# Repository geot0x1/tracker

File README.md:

# Revision 1 [R1]

### Known issues

The 3.3V power supply remains disabled by the battery charger, which pulls the EN pin low with the PG pin. It must be inverted using a BJT.  

Battery connector pins is wrong.  

Crystal has wrong footprint.  

Memory footprint is wrong, too big for the part.  

RX and TX lines on GSM connection are swapped.  

Change the programming port to 1.5mm pitch.

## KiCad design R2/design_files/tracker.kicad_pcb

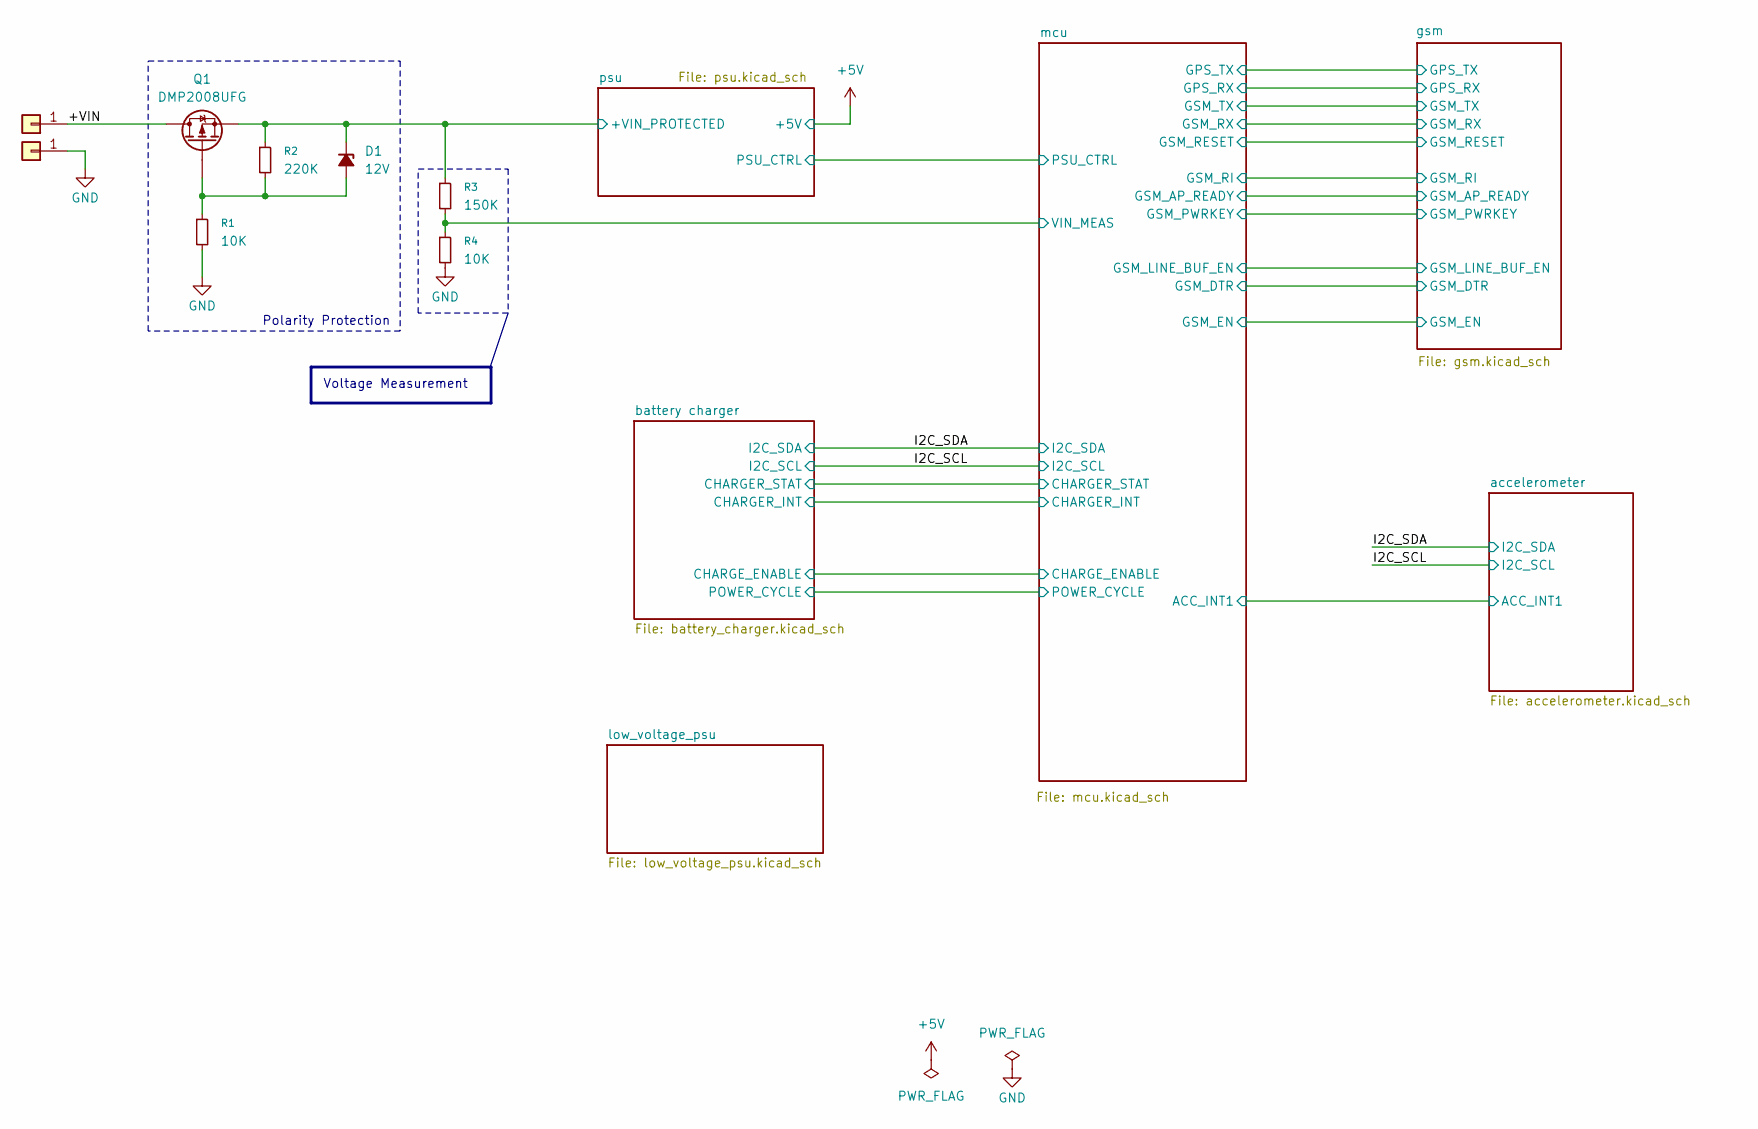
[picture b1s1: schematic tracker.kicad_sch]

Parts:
D1: 12V; D_SOD-323; PartNo PDZ12B,115
J1, J2: Conn_01x01; pad_smd_1.5x3
Q1: DMP2008UFG; Diodes_PowerDI3333-8
R1, R4: 10K; R_0603_1608Metric
R2: 220K; R_0603_1608Metric
R3: 150K; R_0603_1608Metric

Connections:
/+VIN: J1.1 (Pin_1_1), Q1.5 (D)
/mcu/VIN_MEAS: R3.2, R4.1; also elsewhere on the board
/psu/+VIN_PROTECTED: D1.1 (K), Q1.1 (S), Q1.2 (S), Q1.3 (S), R2.1, R3.1; also elsewhere on the board
GND: J2.1 (Pin_1_1), R1.2, R4.2; also elsewhere on the board
unnamed: D1.2 (A), Q1.4 (G), R1.1, R2.2

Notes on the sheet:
Polarity Protection
Voltage Measurement

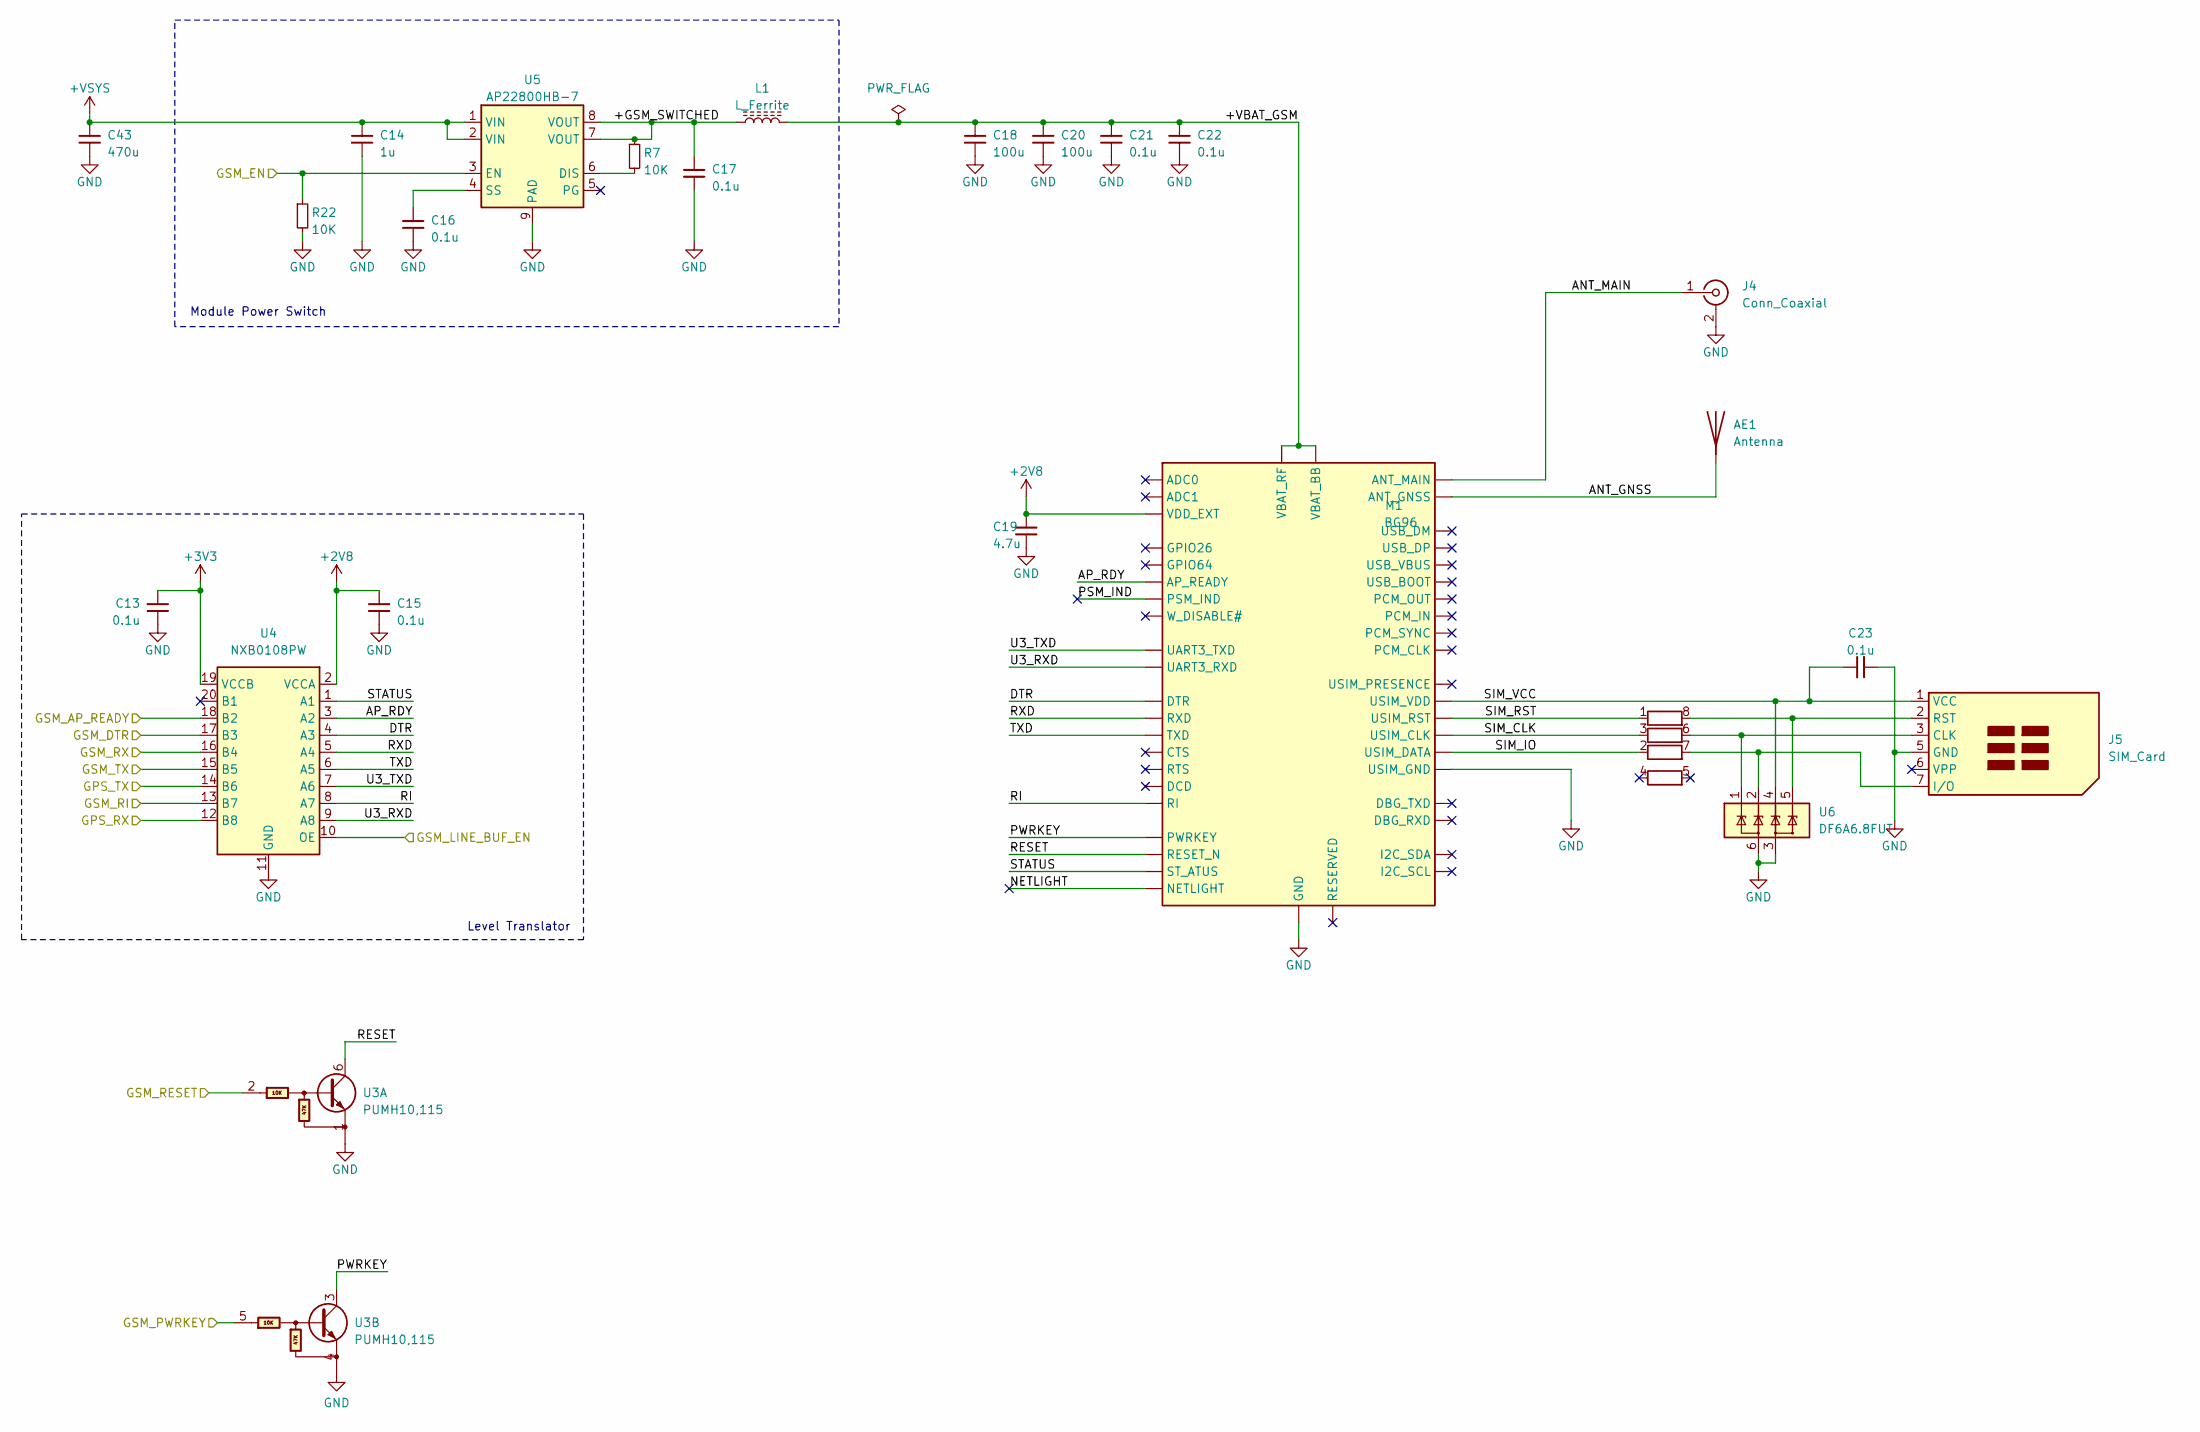
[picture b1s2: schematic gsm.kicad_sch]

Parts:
AE1: Antenna; APAE1575R1820ABDC1
C13, C15, C16, C17, C21, C22, C23: 0.1u; C_0603_1608Metric
C14: 1u; C_0603_1608Metric
C18, C20: 100u; CP_EIA-6032-20_AVX-F
C19: 4.7u; C_0603_1608Metric
C43: 470u; CP_EIA-7343-31_Kemet-D
J4: Conn_Coaxial; U.FL_Molex_MCRF_73412-0110_Vertical
J5: SIM_Card; microSIM_JAE_SF53S006VCBR2000
L1: L_Ferrite; L_0805_2012Metric
M1: BG96; LGA_BG96
R7, R22: 10K; R_0402_1005Metric
RN1: 22R; R_Array_Concave_4x0603
U3: PUMH10,115; SOT-363_SC-70-6
U4: NXB0108PW; TSSOP-20_4.4x6.5mm_P0.65mm
U5: AP22800HB-7; UDFN2116-8_Diodes
U6: DF6A6.8FUT; SOT-363_SC-70-6

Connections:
+2V8: C15.1, C19.1, M1.29 (VDD_EXT), U4.2 (VCCA)
+3V3: C13.1, U4.19 (VCCB); also elsewhere on the board
+VSYS: C14.1, C43.1, U5.1 (VIN), U5.2 (VIN); also elsewhere on the board
/gsm/+GSM_SWITCHED: C17.1, L1.1, R7.1, U5.7 (VOUT), U5.8 (VOUT)
/gsm/+VBAT_GSM: C18.1, C20.1, C21.1, C22.1, L1.2, M1.32 (VBAT_BB), M1.33 (VBAT_BB), M1.52 (VBAT_RF), M1.53 (VBAT_RF), M1.[32,33] (VBAT_BB), M1.[52,53] (VBAT_RF)
/gsm/ANT_GNSS: AE1.1 (A_1), M1.49 (ANT_GNSS)
/gsm/ANT_MAIN: J4.1 (In), M1.60 (ANT_MAIN)
/gsm/AP_RDY: M1.19 (AP_READY), U4.3 (A2)
/gsm/DTR: M1.30 (DTR), U4.4 (A3)
/gsm/GPS_RX: U4.12 (B8); also elsewhere on the board
/gsm/GPS_TX: U4.14 (B6); also elsewhere on the board
/gsm/GSM_AP_READY: U4.18 (B2); also elsewhere on the board
/gsm/GSM_DTR: U4.17 (B3); also elsewhere on the board
/gsm/GSM_EN: R22.1, U5.3 (EN); also elsewhere on the board
/gsm/GSM_LINE_BUF_EN: U4.10 (OE); also elsewhere on the board
/gsm/GSM_PWRKEY: U3.5; also elsewhere on the board
/gsm/GSM_RESET: U3.2; also elsewhere on the board
/gsm/GSM_RI: U4.13 (B7); also elsewhere on the board
/gsm/GSM_RX: U4.16 (B4); also elsewhere on the board
/gsm/GSM_TX: U4.15 (B5); also elsewhere on the board
/gsm/NETLIGHT: M1.21 (NETLIGHT)
/gsm/PSM_IND: M1.1 (PSM_IND)
/gsm/PWRKEY: M1.15 (PWRKEY), U3.3
/gsm/RESET: M1.17 (RESET_N), U3.6
/gsm/RI: M1.39 (RI), U4.8 (A7)
/gsm/RXD: M1.34 (RXD), U4.5 (A4)
/gsm/SIM_CLK: M1.46 (USIM_CLK), RN1.3 (R3.1)
/gsm/SIM_IO: M1.45 (USIM_DATA), RN1.2 (R2.1)
/gsm/SIM_RST: M1.44 (USIM_RST), RN1.1 (R1.1)
/gsm/SIM_VCC: C23.1, J5.1 (VCC), M1.43 (USIM_VDD), U6.4 (IO3)
/gsm/STATUS: M1.20 (ST_ATUS), U4.1 (A1)
/gsm/TXD: M1.35 (TXD), U4.6 (A5)
/gsm/U3_RXD: M1.28 (UART3_RXD), U4.9 (A8)
/gsm/U3_TXD: M1.27 (UART3_TXD), U4.7 (A6)
GND: C13.2, C14.2, C15.2, C16.2, C17.2, C18.2, C19.2, C20.2, C21.2, C22.2, C23.2, C43.2, J4.2 (Ext), J5.5 (GND), M1.3 (GND), M1.31 (GND), M1.47 (USIM_GND), M1.48 (GND), M1.50 (GND), M1.54 (GND), M1.55 (GND), M1.58 (GND), M1.59 (GND), M1.61 (GND), M1.62 (GND), M1.67 (GND), M1.68 (GND), M1.69 (GND), M1.70 (GND), M1.71 (GND), M1.72 (GND), M1.73 (GND), M1.74 (GND), M1.79 (GND), M1.80 (GND), M1.81 (GND), M1.82 (GND), M1.89 (GND), M1.90 (GND), M1.91 (GND), M1.100 (GND), M1.101 (GND), M1.102 (GND), M1.[3,31,48,50,54,55,5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 (GND), R22.2, U3.1, U3.4, U4.11 (GND), U5.9 (PAD), U6.3 (GND), U6.6 (GND); also elsewhere on the board
unnamed: J5.3 (CLK), RN1.6 (R3.2), U6.1 (IO1)
unnamed: J5.7 (I/O), RN1.7 (R2.2), U6.2 (IO2)
unnamed: J5.2 (RST), RN1.8 (R1.2), U6.5 (IO4)
unnamed: R7.2, U5.6 (DIS)
unnamed: C16.1, U5.4 (SS)

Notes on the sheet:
Module Power Switch
Level Translator

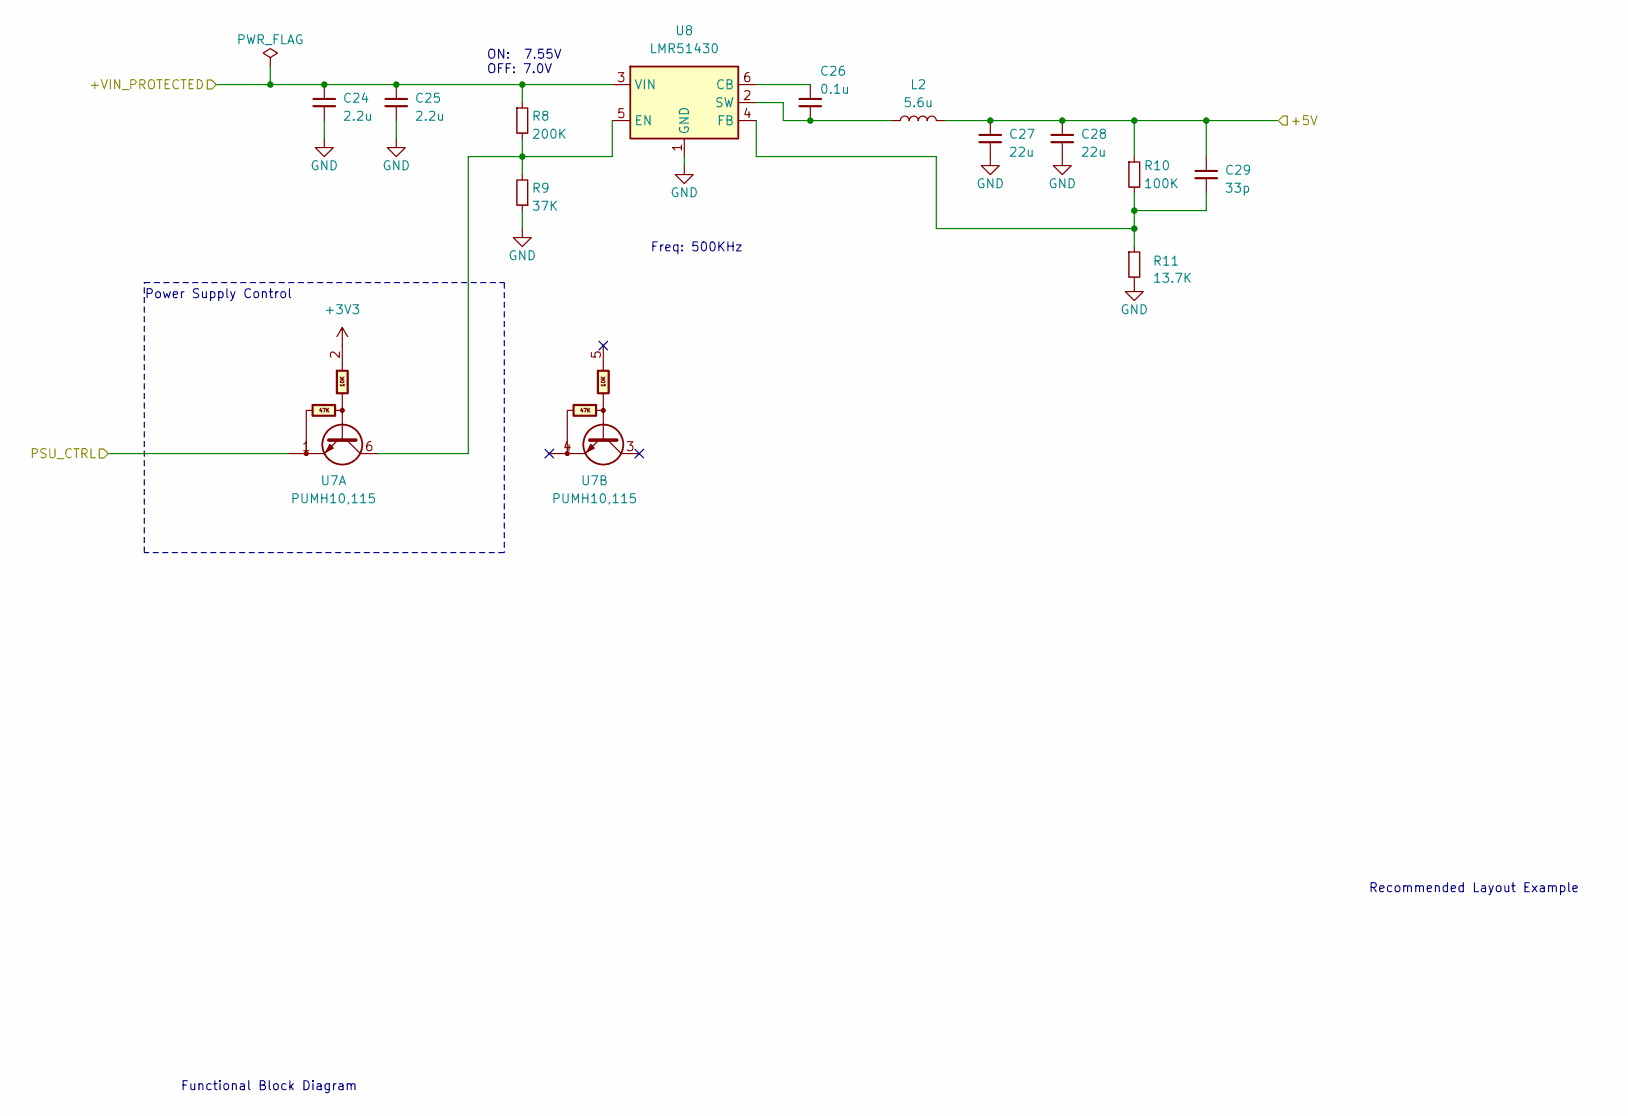
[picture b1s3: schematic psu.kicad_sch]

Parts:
C24, C25: 2.2u; C_1210_3225Metric
C26: 0.1u; C_0603_1608Metric
C27, C28: 22u; C_1210_3225Metric
C29: 33p; C_0402_1005Metric
L2: 5.6u; L_Bourns_SRN8040TA; Part No SRN8040TA-5R6M
R8: 200K; R_0402_1005Metric
R9: 37K; R_0402_1005Metric
R10: 100K; R_0402_1005Metric
R11: 13.7K; R_0402_1005Metric
U7: PUMH10,115; SOT-363_SC-70-6
U8: LMR51430; SOT-23-6

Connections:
+3V3: U7.2; also elsewhere on the board
+5V: C27.1, C28.1, C29.1, L2.2, R10.1; also elsewhere on the board
/mcu/PSU_CTRL: U7.1; also elsewhere on the board
/psu/+VIN_PROTECTED: C24.1, C25.1, R8.1, U8.3 (VIN); also elsewhere on the board
GND: C24.2, C25.2, C27.2, C28.2, R9.1, R11.2, U8.1 (GND); also elsewhere on the board
unnamed: C26.1, U8.6 (CB)
unnamed: R8.2, R9.2, U7.6, U8.5 (EN)
unnamed: C29.2, R10.2, R11.1, U8.4 (FB)
unnamed: C26.2, L2.1, U8.2 (SW)

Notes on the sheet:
Freq: 500KHz
Functional Block Diagram
ON: 7.55V OFF: 7.0V
Power Supply Control
Recommended Layout Example

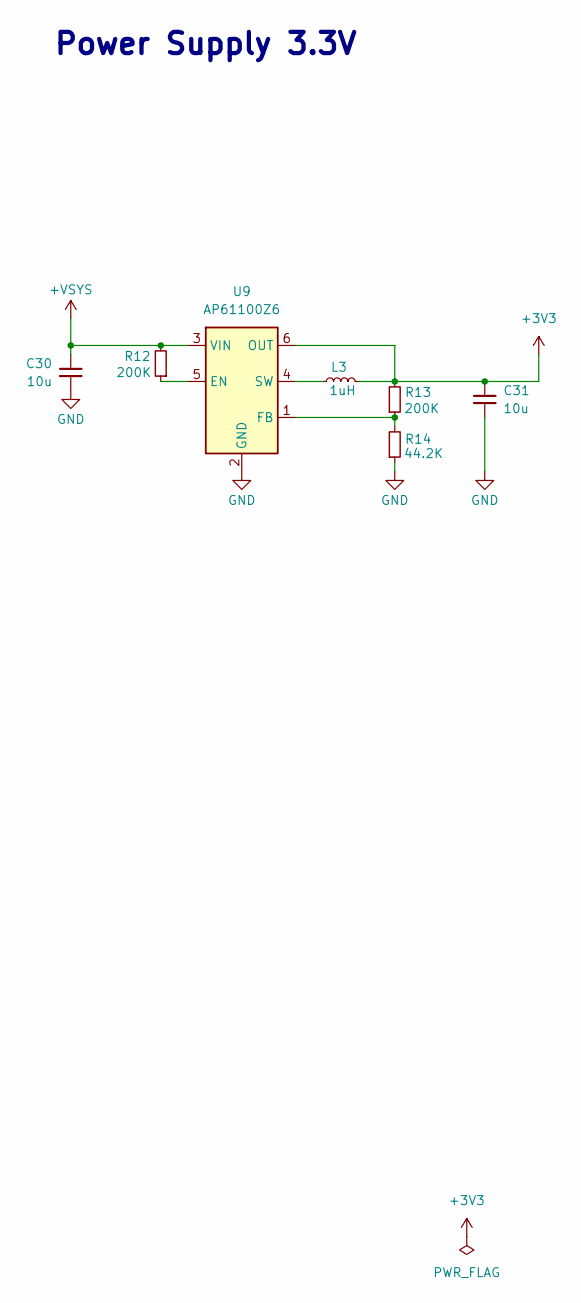
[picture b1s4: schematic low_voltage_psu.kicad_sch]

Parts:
C30, C31: 10u; C_0805_2012Metric
L3: 1uH; L_0806_2016Metric_TAIYO_YUDEN_SMD; PartNo MAKK2016T1R0M
R12, R13: 200K; R_0402_1005Metric
R14: 44.2K; R_0402_1005Metric
U9: AP61100Z6; SOT-563

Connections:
+3V3: C31.1, L3.2, R13.2, U9.6 (OUT); also elsewhere on the board
+VSYS: C30.1, R12.2, U9.3 (VIN); also elsewhere on the board
GND: C30.2, C31.2, R14.1, U9.2 (GND); also elsewhere on the board
unnamed: R12.1, U9.5 (EN)
unnamed: R13.1, R14.2, U9.1 (FB)
unnamed: L3.1, U9.4 (SW)

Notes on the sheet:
Power Supply 3.3V

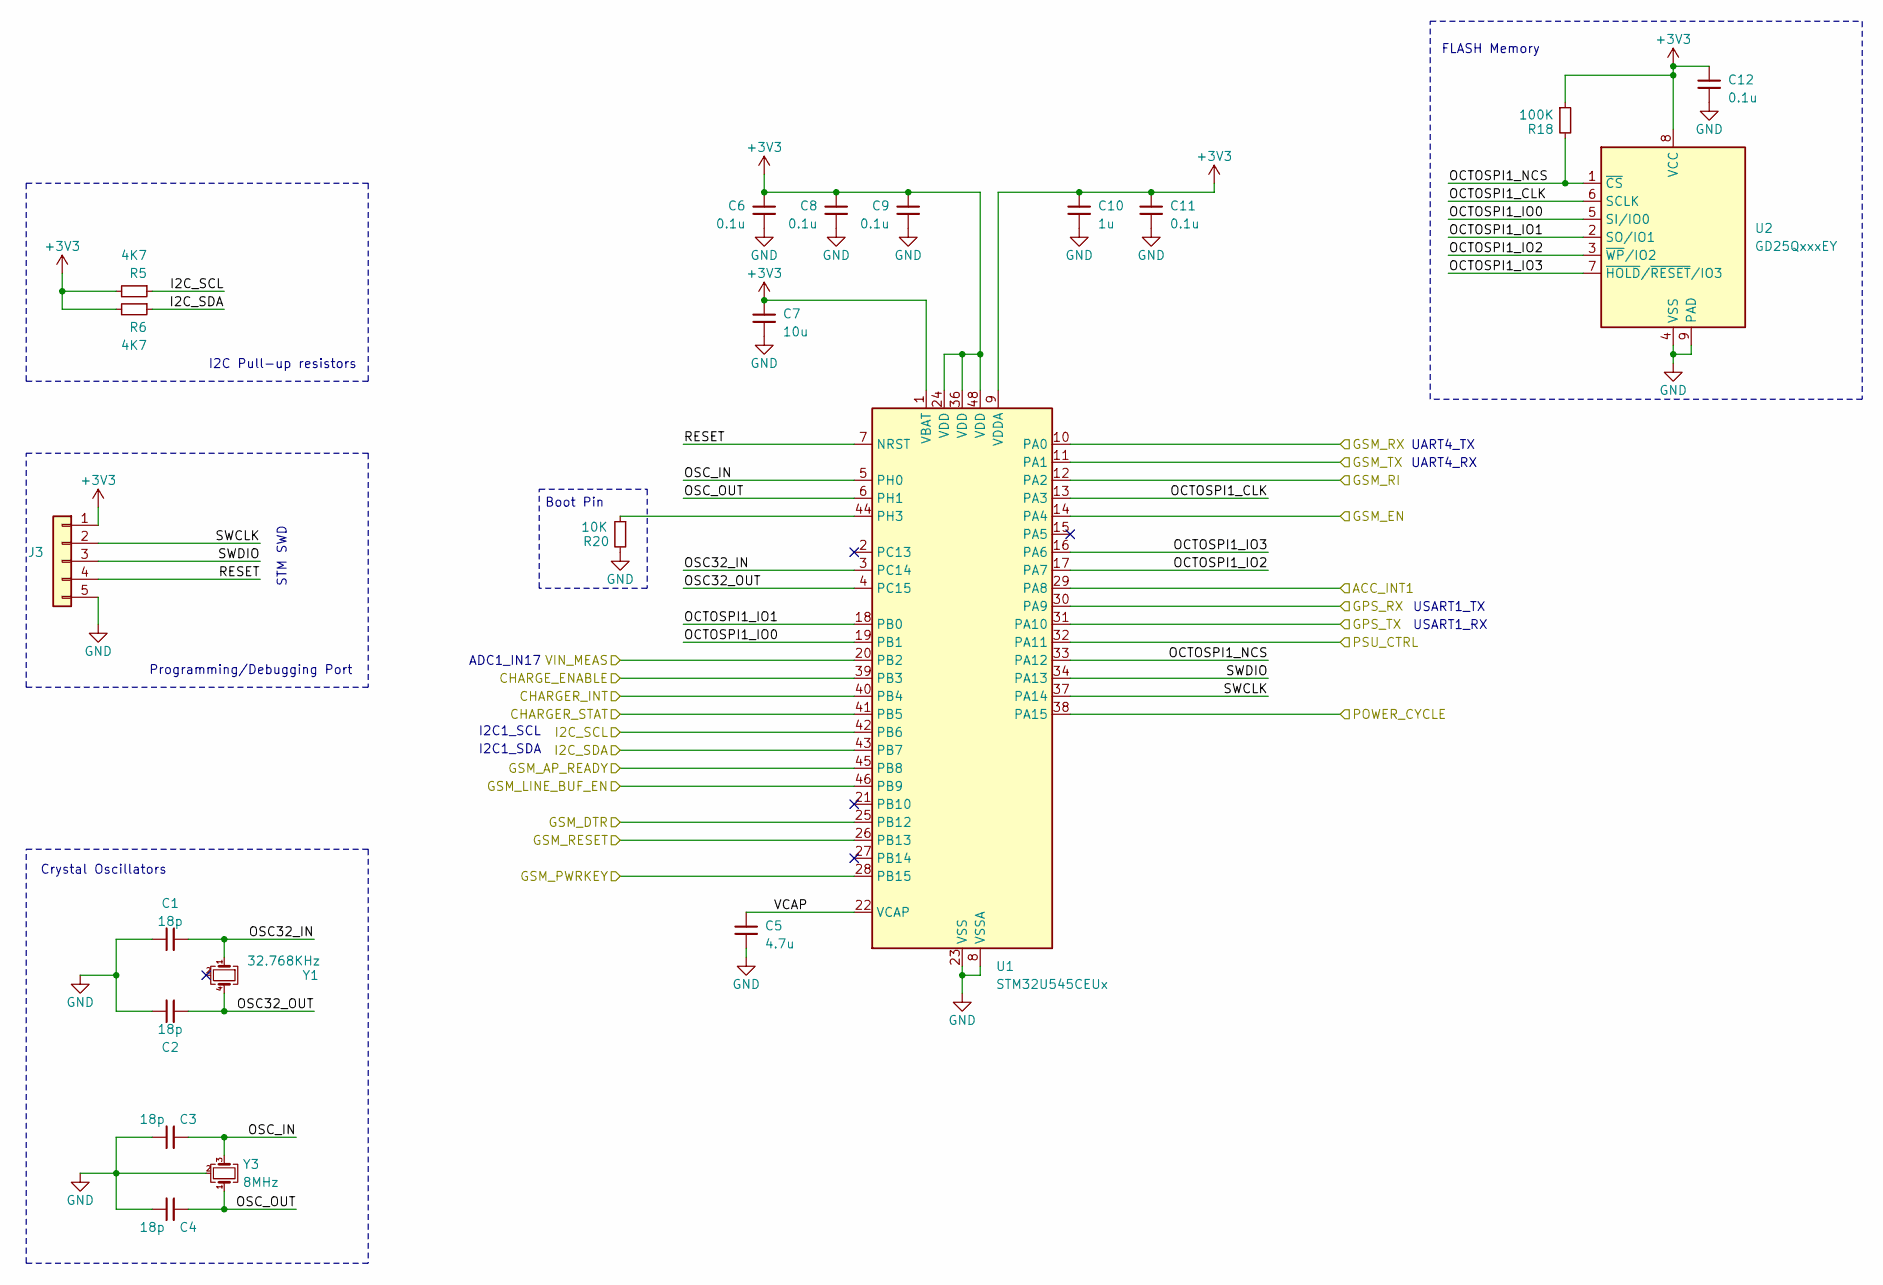
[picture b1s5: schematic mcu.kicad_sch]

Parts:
C1, C2, C3, C4: 18p; C_0402_1005Metric
C5: 4.7u; C_0603_1608Metric
C6, C8, C9, C11, C12: 0.1u; C_0603_1608Metric
C7: 10u; C_0805_2012Metric
C10: 1u; C_0603_1608Metric
J3: Conn_01x05; JST_PH_B5B-PH-SM4-TB_1x05-1MP_P2.00mm_Vertical
R5, R6: 4K7; R_0402_1005Metric
R18: 100K; R_0402_1005Metric
R20: 10K; R_0402_1005Metric
U1: STM32U545CEUx; QFN-48-1EP_7x7mm_P0.5mm_EP5.6x5.6mm
U2: GD25QxxxEY; WSON-8-1EP_8x6mm_P1.27mm_EP3.4x4.3mm
Y1: 32.768KHz; Crystal_SMD_SeikoEpson_MC146-4Pin_6.7x1.5mm
Y3: 8MHz; Crystal_SMD_SeikoEpson_FA238-4Pin_3.2x2.5mm; JLCPCB C49158086

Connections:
+3V3: C6.1, C7.1, C8.1, C9.1, C10.1, C11.1, C12.1, J3.1, R5.2, R6.2, R18.1, U1.1 (VBAT), U1.9 (VDDA), U1.24 (VDD), U1.36 (VDD), U1.48 (VDD), U2.8 (VCC); also elsewhere on the board
/I2C_SCL: R5.1, U1.42 (PB6); also elsewhere on the board
/I2C_SDA: R6.1, U1.43 (PB7); also elsewhere on the board
/accelerometer/ACC_INT1: U1.29 (PA8); also elsewhere on the board
/battery charger/CHARGER_INT: U1.40 (PB4); also elsewhere on the board
/battery charger/CHARGER_STAT: U1.41 (PB5); also elsewhere on the board
/battery charger/CHARGE_ENABLE: U1.39 (PB3); also elsewhere on the board
/battery charger/POWER_CYCLE: U1.38 (PA15); also elsewhere on the board
/gsm/GPS_RX: U1.30 (PA9); also elsewhere on the board
/gsm/GPS_TX: U1.31 (PA10); also elsewhere on the board
/gsm/GSM_AP_READY: U1.45 (PB8); also elsewhere on the board
/gsm/GSM_DTR: U1.25 (PB12); also elsewhere on the board
/gsm/GSM_EN: U1.14 (PA4); also elsewhere on the board
/gsm/GSM_LINE_BUF_EN: U1.46 (PB9); also elsewhere on the board
/gsm/GSM_PWRKEY: U1.28 (PB15); also elsewhere on the board
/gsm/GSM_RESET: U1.26 (PB13); also elsewhere on the board
/gsm/GSM_RI: U1.12 (PA2); also elsewhere on the board
/gsm/GSM_RX: U1.10 (PA0); also elsewhere on the board
/gsm/GSM_TX: U1.11 (PA1); also elsewhere on the board
/mcu/OCTOSPI1_CLK: U1.13 (PA3), U2.6 (SCLK)
/mcu/OCTOSPI1_IO0: U1.19 (PB1), U2.5 (SI/IO0)
/mcu/OCTOSPI1_IO1: U1.18 (PB0), U2.2 (SO/IO1)
/mcu/OCTOSPI1_IO2: U1.17 (PA7), U2.3 (~WP/IO2)
/mcu/OCTOSPI1_IO3: U1.16 (PA6), U2.7 (~HOLD/~RESET/IO3)
/mcu/OCTOSPI1_NCS: R18.2, U1.33 (PA12), U2.1 (~CS)
/mcu/OSC32_IN: C1.2, U1.3 (PC14), Y1.1
/mcu/OSC32_OUT: C2.1, U1.4 (PC15), Y1.4
/mcu/OSC_IN: C3.2, U1.5 (PH0), Y3.3
/mcu/OSC_OUT: C4.2, U1.6 (PH1), Y3.1
/mcu/PSU_CTRL: U1.32 (PA11); also elsewhere on the board
/mcu/RESET: J3.4, U1.7 (NRST)
/mcu/SWCLK: J3.2, U1.37 (PA14)
/mcu/SWDIO: J3.3, U1.34 (PA13)
/mcu/VCAP: C5.1, U1.22 (VCAP)
/mcu/VIN_MEAS: U1.20 (PB2); also elsewhere on the board
GND: C1.1, C2.2, C3.1, C4.1, C5.2, C6.2, C7.2, C8.2, C9.2, C10.2, C11.2, C12.2, J3.5, R20.2, U1.8 (VSSA), U1.23 (VSS), U1.35 (VSS), U1.47 (VSS), U1.49 (VSS), U2.4 (VSS), U2.9 (PAD), Y3.2 (G), Y3.4 (G); also elsewhere on the board
unnamed: R20.1, U1.44 (PH3)

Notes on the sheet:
USART1_RX
UART4_TX
STM SWD
Boot Pin
I2C1_SCL
I2C1_SDA
Crystal Oscillators
UART4_RX
USART1_TX
Programming/Debugging Port
FLASH Memory
ADC1_IN17
I2C Pull-up resistors

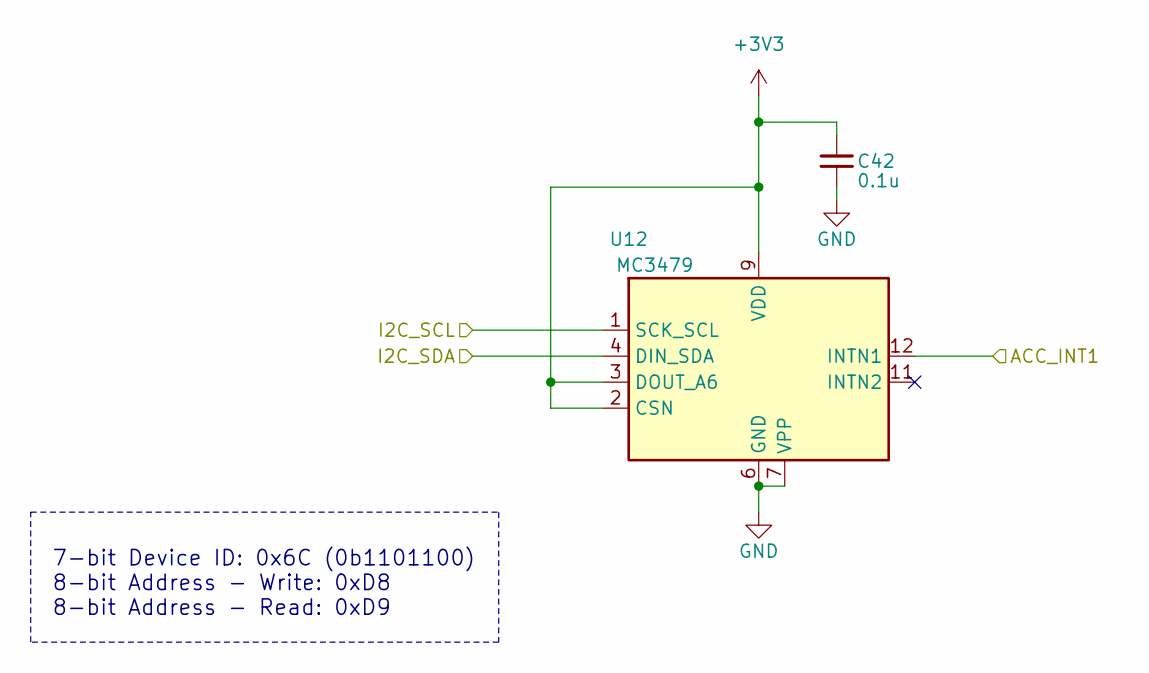
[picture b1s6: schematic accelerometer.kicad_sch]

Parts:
C42: 0.1u; C_0603_1608Metric
U12: MC3479; LGA-12_2x2mm_P0.5mm

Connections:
+3V3: C42.1, U12.2 (CSN), U12.3 (DOUT_A6), U12.9 (VDD); also elsewhere on the board
/I2C_SCL: U12.1 (SCK_SCL); also elsewhere on the board
/I2C_SDA: U12.4 (DIN_SDA); also elsewhere on the board
/accelerometer/ACC_INT1: U12.12 (INTN1); also elsewhere on the board
GND: C42.2, U12.6 (GND), U12.7 (VPP); also elsewhere on the board

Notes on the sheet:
7-bit Device ID: 0x6C (0b1101100) 8-bit Address - Write: 0xD8 8-bit Address - Read: 0xD9

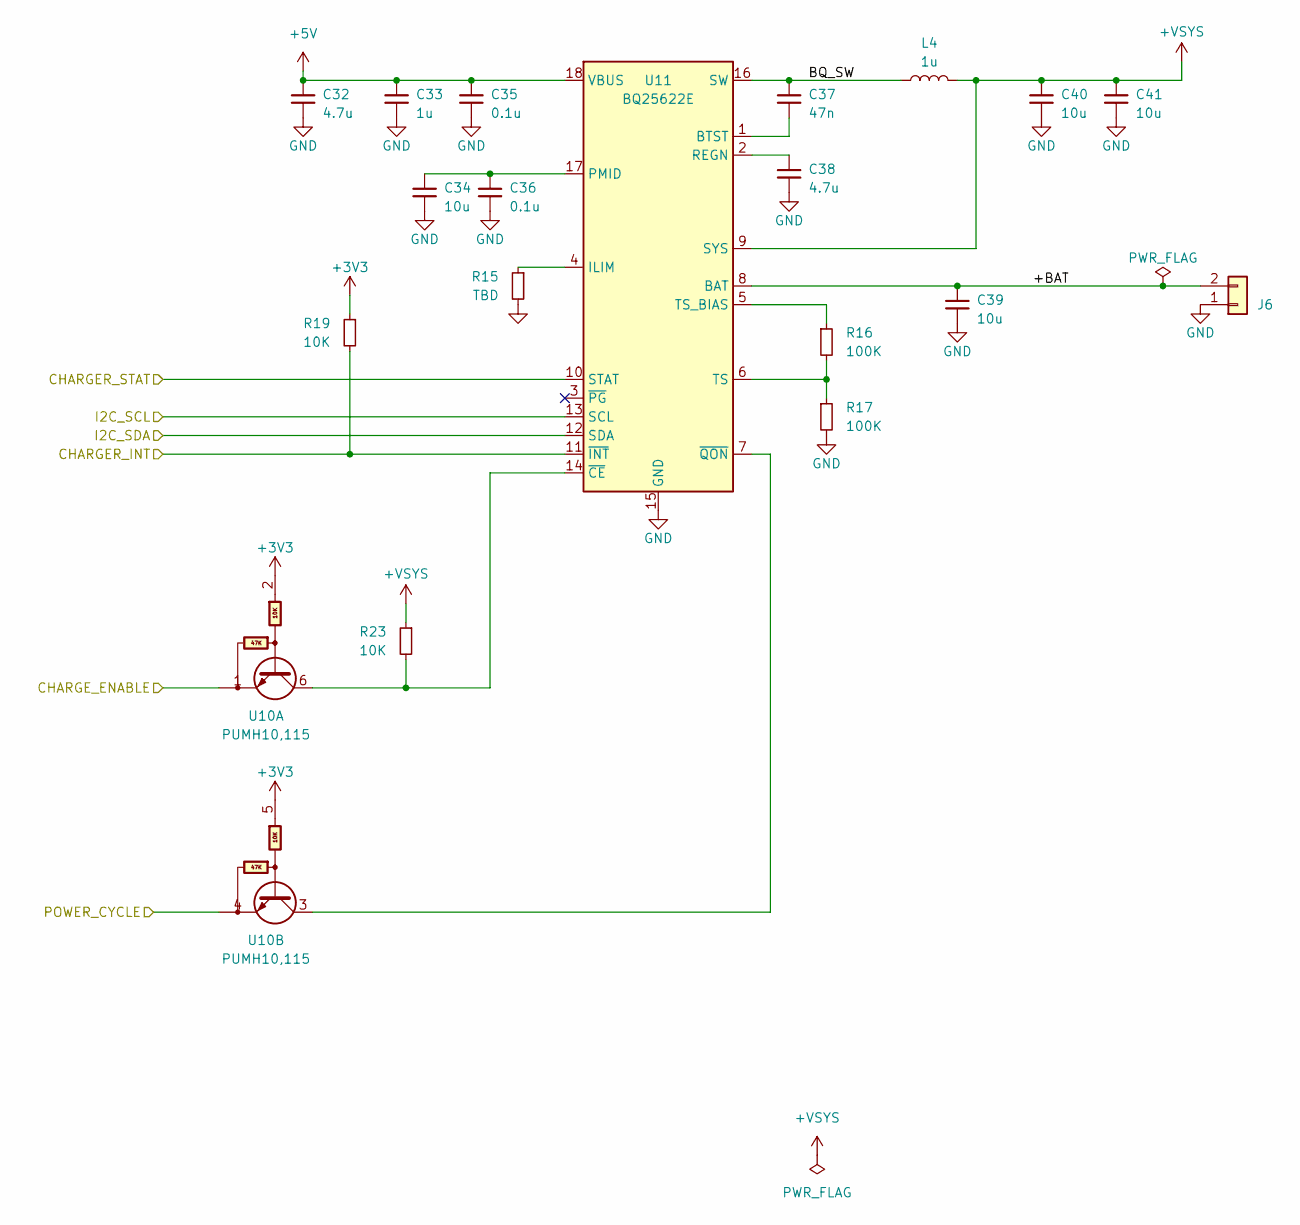
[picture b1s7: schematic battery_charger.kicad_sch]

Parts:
C32: 4.7u; C_0805_2012Metric
C33: 1u; C_0603_1608Metric
C34, C39, C40, C41: 10u; C_0805_2012Metric
C35, C36: 0.1u; C_0603_1608Metric
C37: 47n; C_0402_1005Metric
C38: 4.7u; C_0603_1608Metric
J6: Conn_01x02; JST_XH_B2B-XH-A_1x02_P2.50mm_Vertical
L4: 1u; Inductor_TYA252012
R15: TBD; R_0402_1005Metric
R16, R17: 100K; R_0402_1005Metric
R19, R23: 10K; R_0402_1005Metric
U10: PUMH10,115; SOT-363_SC-70-6
U11: BQ25622E

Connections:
+3V3: R19.1, U10.2, U10.5; also elsewhere on the board
+5V: C32.1, C33.1, C35.1, U11.18 (VBUS); also elsewhere on the board
+VSYS: C40.1, C41.1, L4.2, R23.1, U11.9 (SYS); also elsewhere on the board
/I2C_SCL: U11.13 (SCL); also elsewhere on the board
/I2C_SDA: U11.12 (SDA); also elsewhere on the board
/battery charger/+BAT: C39.1, J6.2, U11.8 (BAT)
/battery charger/BQ_SW: C37.1, L4.1, U11.16 (SW)
/battery charger/CHARGER_INT: R19.2, U11.11 (~INT); also elsewhere on the board
/battery charger/CHARGER_STAT: U11.10 (STAT); also elsewhere on the board
/battery charger/CHARGE_ENABLE: U10.1; also elsewhere on the board
/battery charger/POWER_CYCLE: U10.4; also elsewhere on the board
GND: C32.2, C33.2, C34.2, C35.2, C36.2, C38.2, C39.2, C40.2, C41.2, J6.1, R15.2, R17.2, U11.15 (GND); also elsewhere on the board
unnamed: C37.2, U11.1 (BTST)
unnamed: R15.1, U11.4 (ILIM)
unnamed: C34.1, C36.1, U11.17 (PMID)
unnamed: C38.1, U11.2 (REGN)
unnamed: R16.2, R17.1, U11.6 (TS)
unnamed: R16.1, U11.5 (TS_BIAS)
unnamed: R23.2, U10.6, U11.14 (~CE)
unnamed: U10.3, U11.7 (~QON)

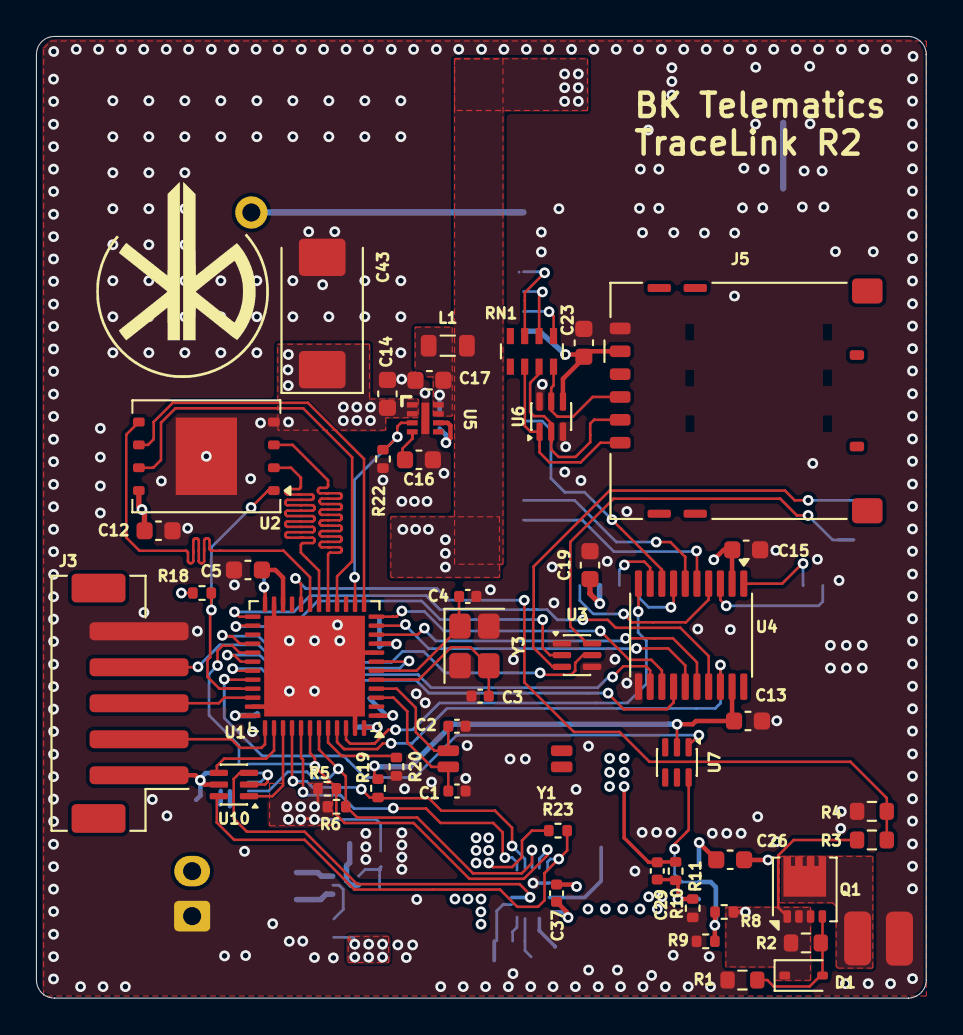
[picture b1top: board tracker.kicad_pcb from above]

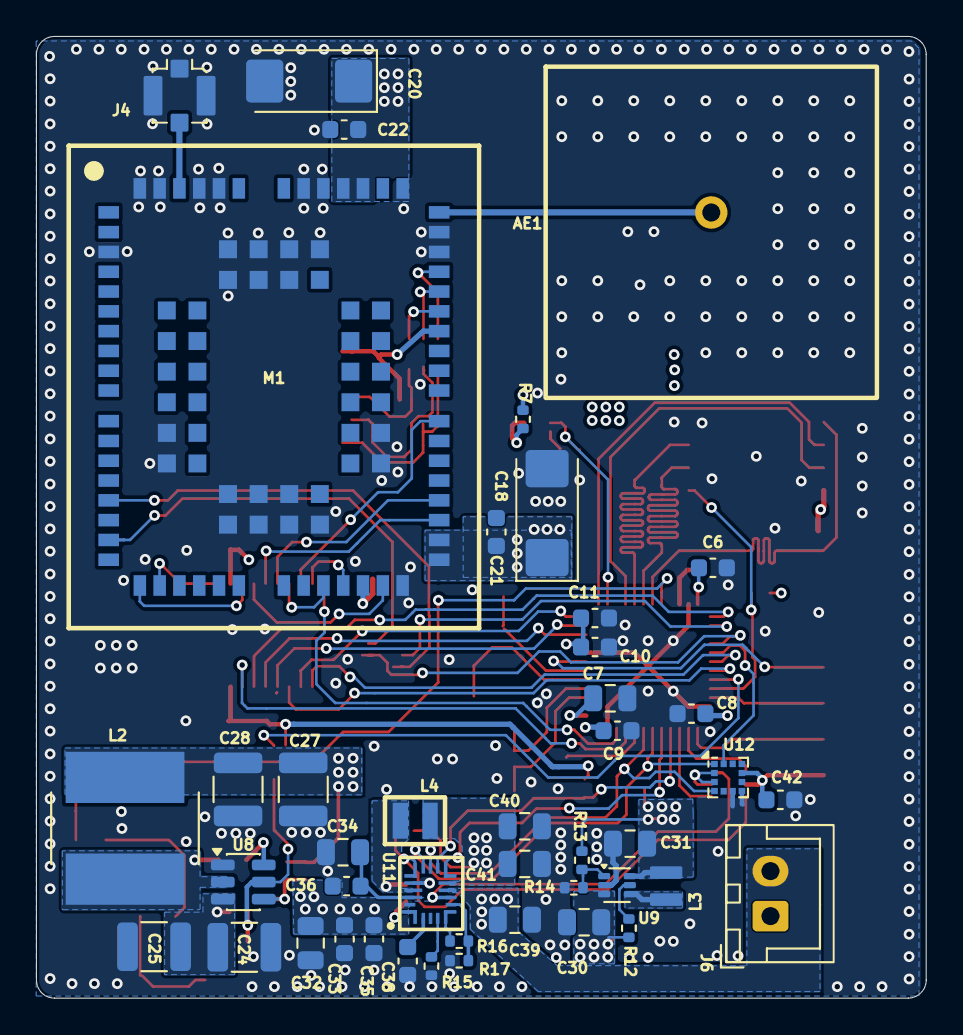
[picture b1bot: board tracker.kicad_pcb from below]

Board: 4 copper layers, 49.4 x 53.4 mm, 94 parts (44 on the bottom side), 83 nets.

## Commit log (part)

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2025-09-27 init
2025-09-30 save
2025-10-02 save project
2025-10-19 edits
2025-10-27 edit silkscreen
2025-10-28 first version
2025-10-28 Deleted files
2025-10-28 rename dir
2025-11-02 Added CS pullup
2025-11-13 First review.
2025-11-13 Added gerbers
2025-11-26 Changed values in schematic
2025-12-10 Added README md file
2025-12-18 added issues in readme
2025-12-19 Added issue
2025-12-19 Added files into R1 directory
2025-12-23 Added R2
2025-12-24 Added test points
2026-01-01 added capacitor 470u
